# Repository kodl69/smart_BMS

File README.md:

# smart_BMS
ATTINY85 module based BMS with open HW and SW

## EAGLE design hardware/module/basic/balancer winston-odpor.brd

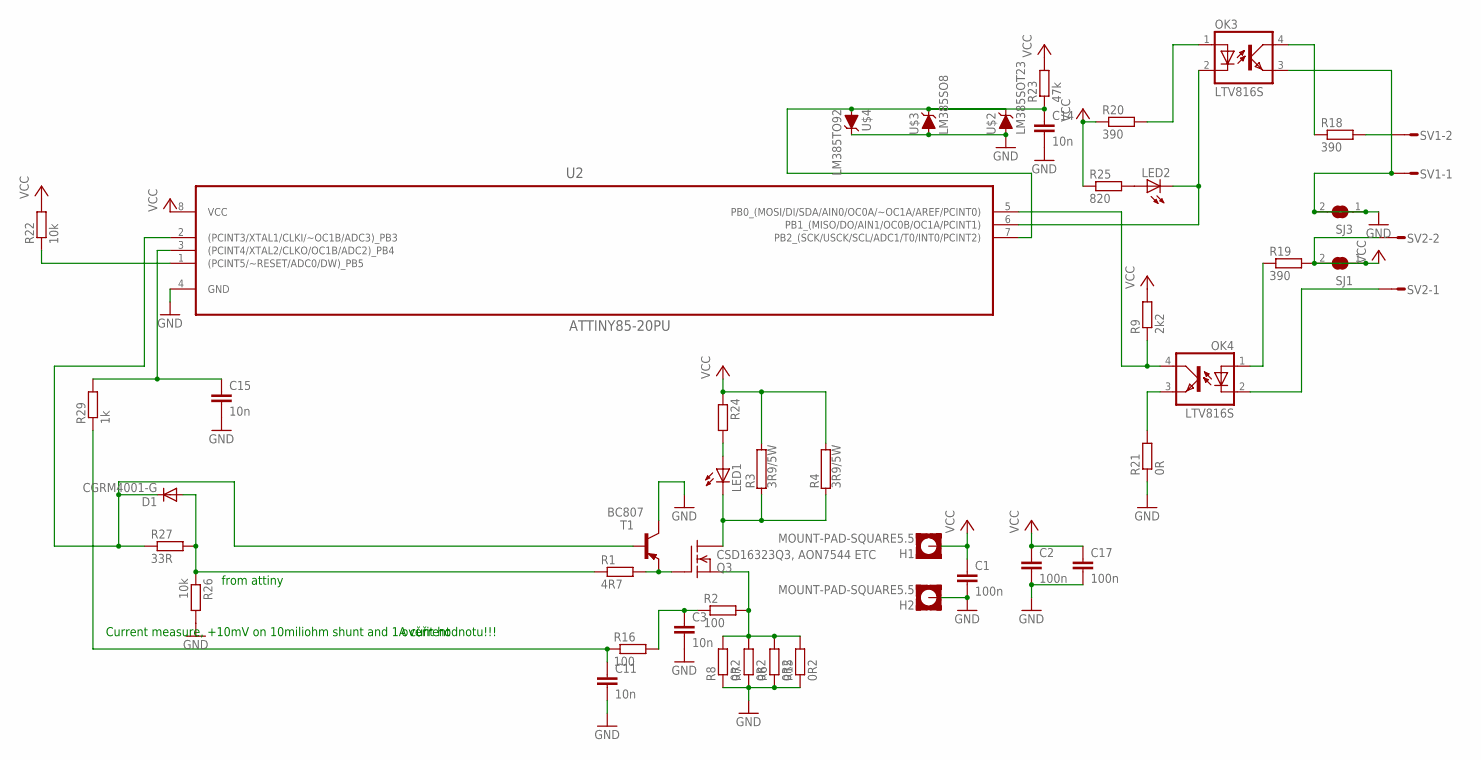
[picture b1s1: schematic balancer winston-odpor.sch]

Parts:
C1, C2, C17: 100n; C1210K
C3, C11, C14, C15: 10n; C0603
D1: CGRM4001-G; SOD-123_MINI-SMA
H1, H2: MOUNT-PAD-SQUARE5.5; 5,5-PAD-SQUARE
LED1, LED2: LED3MM
OK3, OK4: LTV816S; SMD4
Q3: CSD16323Q3, AON7544 ETC; SON33X33
R1: 4R7; R0603
R2, R16: 100; R0603
R3, R4: 3R9/5W; HPS932
R6, R7, R8, R15: 0R2; M1206
R9: 2k2; R0603
R18, R19, R20: 390; R0603
R21: 0R; R0603
R22: 10k; R0805
R23: 47k; R0603
R24: R-EU_R0603; R0603
R25: 820; R0805
R26: 10k; R0603
R27: 33R; R0603
R29: 1k; R0603
SJ1, SJ3: SJ
SV1, SV2: S02P
T1: BC807; SOT23-BEC
U2: ATTINY85-20PU; DIP254P762X533-8
U$2: LM385SOT23; SOT23-3
U$3: LM385SO8; SO08
U$4: LM385TO92; TO-92

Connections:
GND: C1.2, C2.2, C3.2, C11.2, C14.2, C15.2, C17.2, H2.B5,5, OK3.3 (EMIT), R6.1, R7.1, R8.1, R15.1, R21.1, R26.2, SJ3.1, SJ3.2, SV1.1, T1.C, U2.4 (GND), U$2.1 (A), U$3.8 (A), U$4.3 (C)
unnamed: C3.1, R2.1, R16.2
unnamed: Q3.4 (G), R1.2, T1.E
unnamed: Q3.1 (S), Q3.2 (S), Q3.3 (S), R2.2, R6.2, R7.2, R8.2, R15.2
unnamed: C15.1, R29.2, U2.3 ((PCINT4/XTAL2/CLKO/OC1B/ADC2)_PB4)
unnamed: C11.1, R16.1, R29.1
unnamed: LED1.K (C), Q3.EXP (D), R3.1, R4.1
unnamed: LED2.K (C), OK3.2 (C), U2.6 (PB1_(MISO/DO/AIN1/OC0B/OC1A/PCINT1))
unnamed: OK4.1 (A), R19.1
unnamed: OK4.2 (C), SV2.1
unnamed: R18.2, SV1.2
unnamed: R22.1, U2.1 ((PCINT5/~RESET/ADC0/DW)_PB5)
unnamed: D1.A, R1.1, R26.1, R27.2
unnamed: D1.C, R27.1, T1.B, U2.2 ((PCINT3/XTAL1/CLKI/~OC1B/ADC3)_PB3)
unnamed: LED1.A, R24.2
unnamed: LED2.A, R25.2
unnamed: OK3.1 (A), R20.2
unnamed: OK3.4 (COL), R18.1
unnamed: C14.1, R23.1, U2.7 (PB2_(SCK/USCK/SCL/ADC1/T0/INT0/PCINT2)), U$2.2 (C), U$3.4 (C), U$4.2 (A)
unnamed: OK4.3 (EMIT), R21.2
unnamed: OK4.4 (COL), R9.1, U2.5 (PB0_(MOSI/DI/SDA/AIN0/OC0A/~OC1A/AREF/P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)
VCC: C1.1, C2.1, C17.1, H1.B5,5, R3.2, R4.2, R9.2, R19.2, R20.1, R22.2, R23.2, R24.1, R25.1, SJ1.1, SJ1.2, SV2.2, U2.8 (VCC)

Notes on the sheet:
from attiny
Current measure, +10mV on 10miliohm shunt and 1A current
ověřit hodnotu!!!

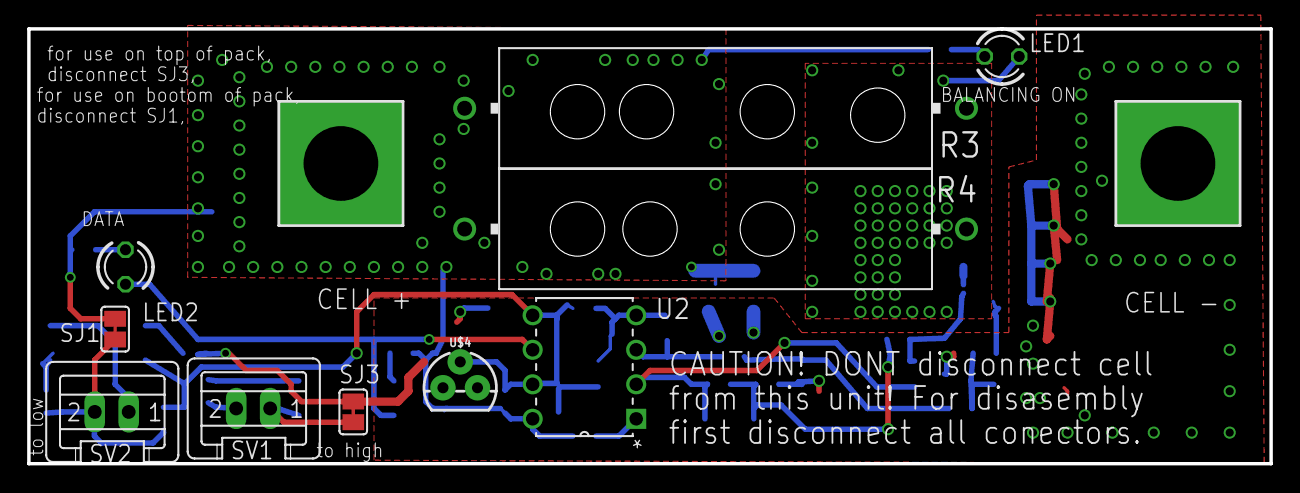
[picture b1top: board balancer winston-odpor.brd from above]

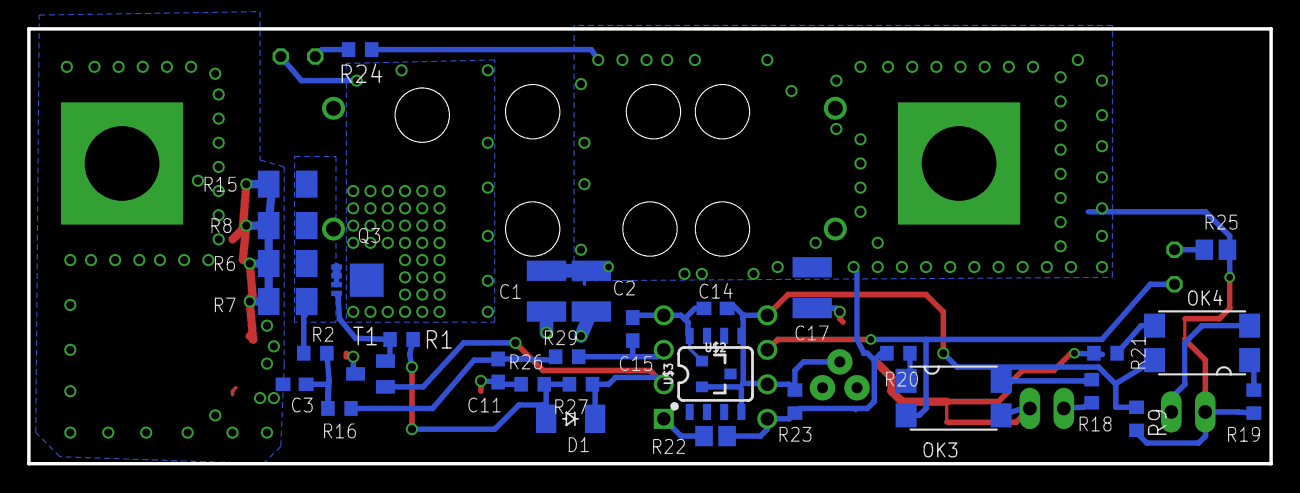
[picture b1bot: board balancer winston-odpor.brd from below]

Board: 2 copper layers, 91.4 x 32.0 mm, 45 parts (33 on the bottom side), 22 nets.

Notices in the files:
parts and their libraries:
SparkFun-DiscreteSemi: Licensing: Creative Commons ShareAlike 4.0 International - https://creativecommons.org/licenses/by-sa/4.0
